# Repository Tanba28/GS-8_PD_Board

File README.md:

# GS-8_PD_Board
GS-8 Parachute Deployment Board

Master project -> [project-arrows/GS-8](https://github.com/project-arrows/GS-8)

## Overview
 * GS-8パラシュート開放基板

## Role
 * 気圧をロギングする。
 * 頂点検知を行う。
 * 開放用アクチュエータ(サーボモータ)を駆動する。

## Link
 * [Tanba28/GS-8_PM_Board](https://github.com/Tanba28/GS-8_PM_Board)
 * [Tanba28/GS-8_Motion_Logger](https://github.com/Tanba28/GS-8_Motion_Logger)
 * [Tanba28/GS-8_Barometer](https://github.com/Tanba28/GS-8_Barometer)
 * [Tanba28/GS-8_Relay_Board](https://github.com/Tanba28/GS-8_Relay_Board)
 * [ringo156/GS-8_ACCLRM_Board](https://github.com/ringo156/GS-8_ACCLRM_Board)
 * [takamasavvv/RCT-X_Logger](https://github.com/takamasavvv/RCT-X-Logger)
 * [takamasavvv/RCT-X-Telemetry](https://github.com/takamasavvv/RCT-X-Telemetry)
 
## LICENSE
MIT License

Copyright (c) 2019 Tanba28

Permission is hereby granted, free of charge, to any person obtaining a copy
of this software and associated documentation files (the "Software"), to deal
in the Software without restriction, including without limitation the rights
to use, copy, modify, merge, publish, distribute, sublicense, and/or sell
copies of the Software, and to permit persons to whom the Software is
furnished to do so, subject to the following conditions:

The above copyright notice and this permission notice shall be included in all
copies or substantial portions of the Software.

THE SOFTWARE IS PROVIDED "AS IS", WITHOUT WARRANTY OF ANY KIND, EXPRESS OR
IMPLIED, INCLUDING BUT NOT LIMITED TO THE WARRANTIES OF MERCHANTABILITY,
FITNESS FOR A PARTICULAR PURPOSE AND NONINFRINGEMENT. IN NO EVENT SHALL THE
AUTHORS OR COPYRIGHT HOLDERS BE LIABLE FOR ANY CLAIM, DAMAGES OR OTHER
LIABILITY, WHETHER IN AN ACTION OF CONTRACT, TORT OR OTHERWISE, ARISING FROM,
OUT OF OR IN CONNECTION WITH THE SOFTWARE OR THE USE OR OTHER DEALINGS IN THE
SOFTWARE.

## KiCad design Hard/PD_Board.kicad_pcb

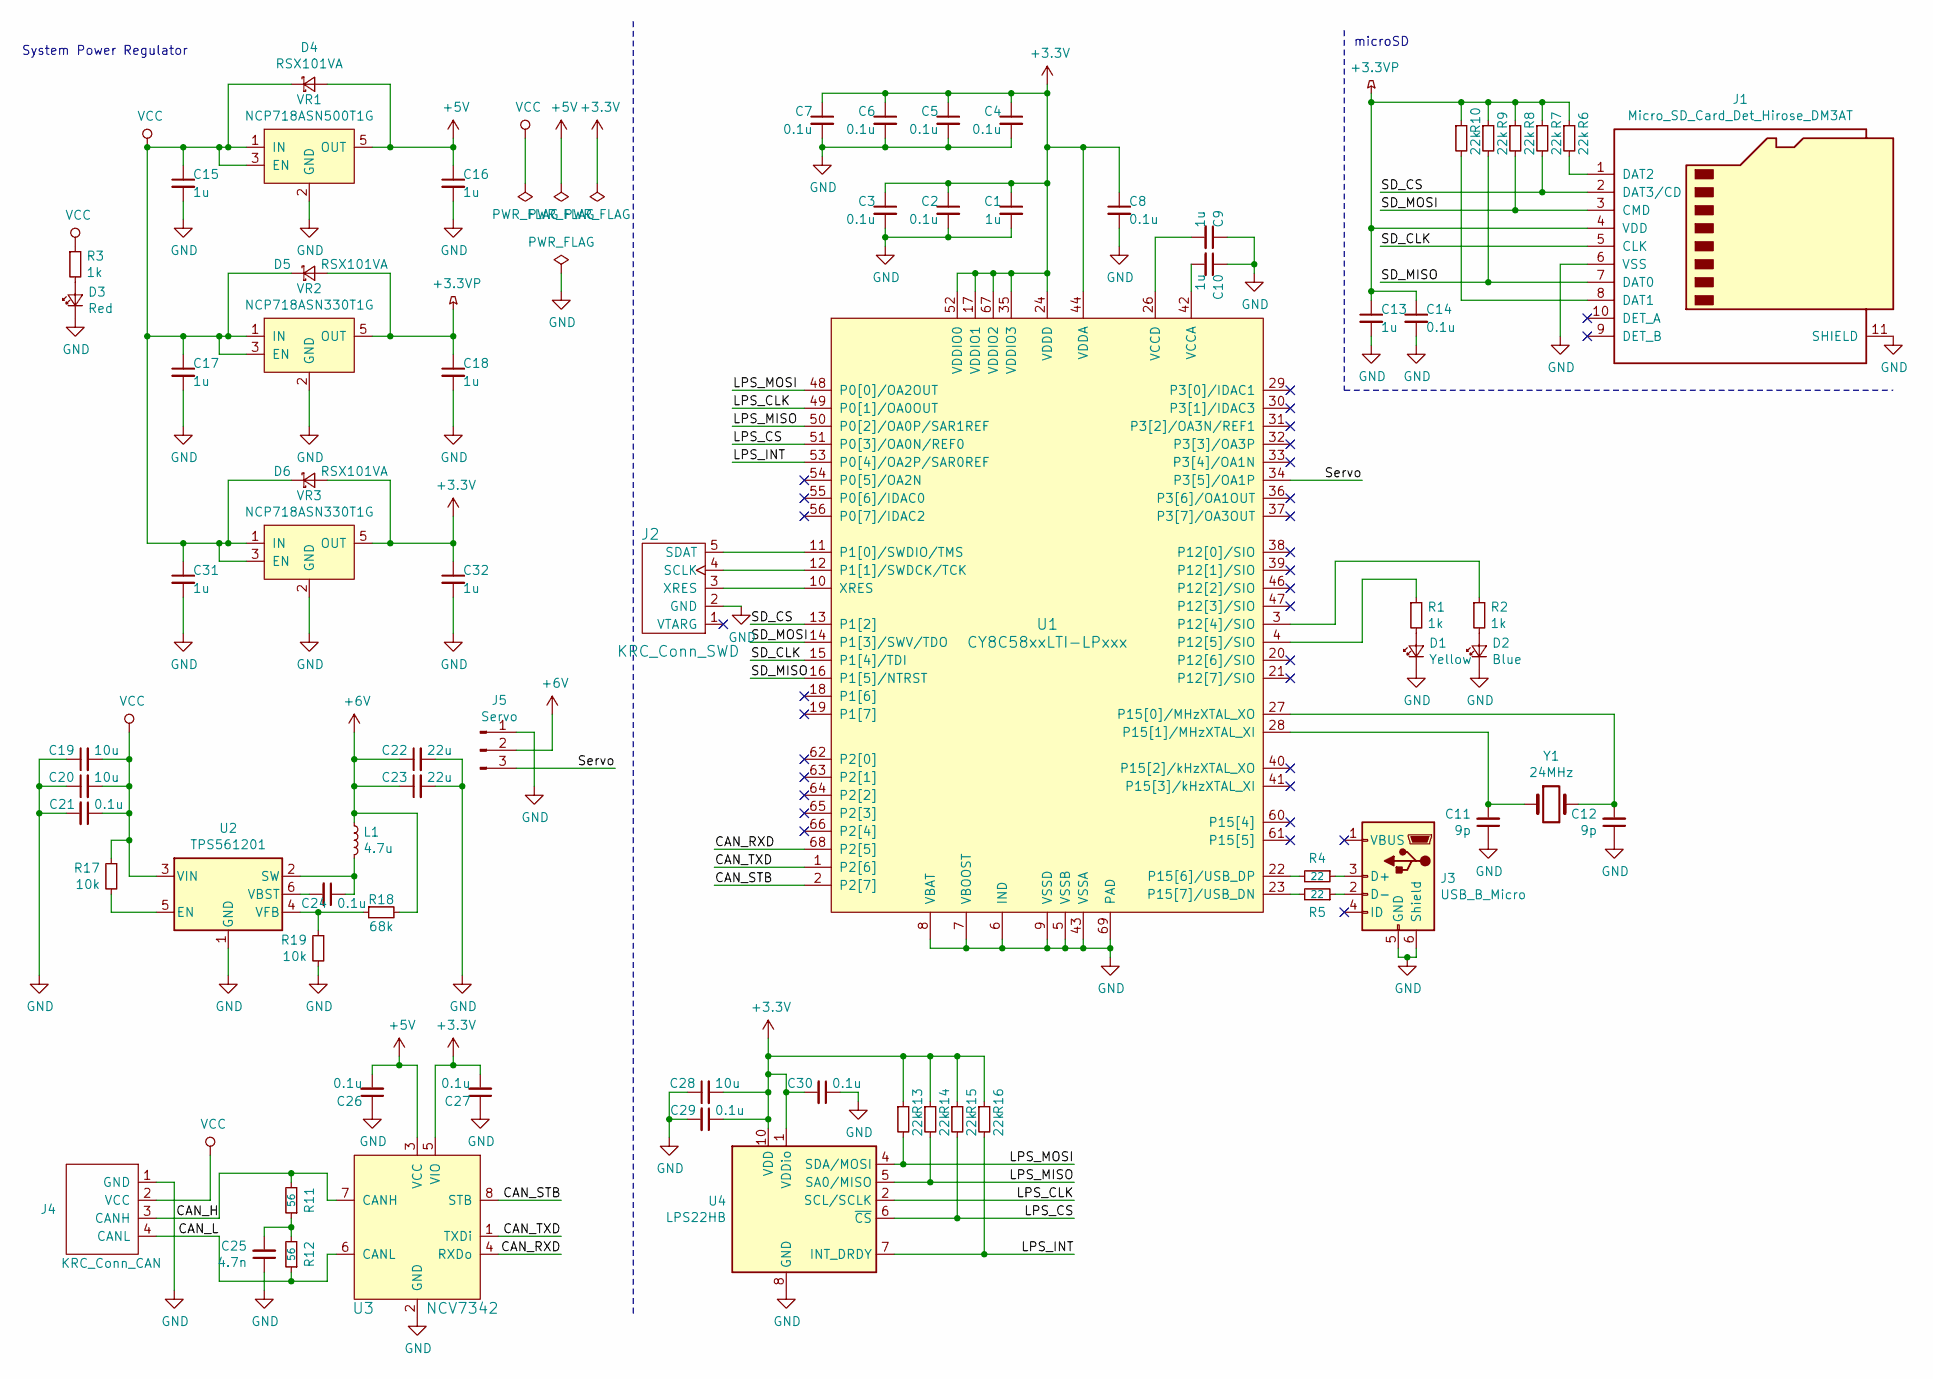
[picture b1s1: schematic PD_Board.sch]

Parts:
C1, C9, C10, C13, C15, C16, C17, C18, C31, C32: 1u; C_0402_1005Metric; MPN GRM155R61E105KA12D
C2, C3, C4, C5, C6, C7, C8, C14, C21, C24, C26, C27, C29, C30: 0.1u; C_0402_1005Metric; MPN GRM155R62A104KE14D
C11, C12: 9p; C_0402_1005Metric; MPN GRM1555C1H9R0DA01D
C19, C20, C28: 10u; C_0603_1608Metric; MPN GRM188R6YA106MA73D
C22, C23: 22u; C_0805_2012Metric; MPN GRM21BR61E226ME44K
C25: 4.7n; C_0402_1005Metric; MPN GRM155R71H472KA01D
D1: Yellow; LED_0603_1608Metric
D2: Blue; LED_0603_1608Metric
D3: Red; LED_0603_1608Metric
D4, D5, D6: RSX101VA; D_TUMD2; MPN RSX101VAM-30TR
J1: Micro_SD_Card_Det_Hirose_DM3AT; microSD_HC_Hirose_DM3AT-SF-PEJM5; MPN DM3AT-SF-PEJM5
J2: KRC_Conn_SWD; JST_JQ_05JQ-BT_1x05_P2.5mm_Vertical; MPN 05JQ-BT
J3: USB_B_Micro; Hirose_ZX_ZX62D-B-5P8; MPN ZX62D-B-5P8(30)
J4: KRC_Conn_CAN; JST_XH_S4B-XH-A_1x04_P2.50mm_Horizontal; MPN S4B-XH-A
J5: Servo; Hirose_DF1E_DF1E-3P-2.5DS_1x03_P2.5mm_Vertical; MPN DF1EC-3P-2.5DSA(35)
L1: 4.7u; L_Taiyo-Yuden_NR-50xx; MPN NRS5020T4R7MMGJ
R1, R2, R3: 1k; R_0402_1005Metric; MPN ERJ-2GEJ102X
R4, R5: 22; R_0402_1005Metric; MPN ERJ-2GEJ220X
R6, R7, R8, R9, R10, R13, R14, R15, R16: 22k; R_0402_1005Metric; MPN ERJ-2RKF2202X
R11, R12: 56; R_0402_1005Metric; MPN ERJ-2GEJ560X
R17, R19: 10k; R_0402_1005Metric; MPN ERJ-2GEJ103X
R18: 68k; R_0402_1005Metric; MPN ERJ-2GEJ103X
U1: CY8C58xxLTI-LPxxx; Cypress_QFN-68_EP_8x8_Pitch0.4mm; MPN CY8C5868LTI-LP039
U2: TPS561201; SOT-23-6; MPN TPS561201DDCT
U3: NCV7342; DFN-8-1EP_3x3mm_P0.65mm_EP1.55x2.4mm; MPN NCV7342MW3R2G
U4: LPS22HB; ST_HLGA-10_2.5x2.5mm_P0.6mm_LayoutBorder3x2y
VR1: NCP718ASN500T1G; TSOT-23-5; MPN NCP718ASN500T1G
VR2, VR3: NCP718ASN330T1G; TSOT-23-5; MPN NCP718ASN330T1G
Y1: 24MHz; Crystal_Murata_XRCHA; MPN XRCHA24M000F0A01R0

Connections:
+3.3VP: C13.1, C14.1, C18.1, D5.2 (A), J1.4 (VDD), R6.1, R7.1, R8.1, R9.1, R10.1, VR2.5 (OUT)
+3V3: C1.1, C2.1, C3.1, C4.1, C5.1, C6.1, C7.1, C8.1, C27.2, C28.2, C29.1, C30.2, C32.1, D6.2 (A), R13.1, R14.1, R15.1, R16.1, U1.17 (VDDIO1), U1.24 (VDDD), U1.35 (VDDIO3), U1.44 (VDDA), U1.52 (VDDIO0), U1.59 (VDDD), U1.67 (VDDIO2), U3.5 (VIO), U4.1 (VDDio), U4.10 (VDD), VR3.5 (OUT)
+5V: C16.1, C26.2, D4.2 (A), U3.3 (VCC), VR1.5 (OUT)
+6V: C22.1, C23.1, J5.2, L1.1, R18.2
/CAN_H: J4.3 (CANH), R11.2, U3.7 (CANH)
/CAN_L: J4.4 (CANL), R12.1, U3.6 (CANL)
/CAN_RXD: U1.68 (P2[5]), U3.4 (RXDo)
/CAN_STB: U1.2 (P2[7]), U3.8 (STB)
/CAN_TXD: U1.1 (P2[6]), U3.1 (TXDi)
/LPS_CLK: U1.49 (P0[1]/OA0OUT), U4.2 (SCL/SCLK)
/LPS_CS: R15.2, U1.51 (P0[3]/OA0N/REF0), U4.6 (~CS)
/LPS_INT: R16.2, U1.53 (P0[4]/OA2P/SAR0REF), U4.7 (INT_DRDY)
/LPS_MISO: R14.2, U1.50 (P0[2]/OA0P/SAR1REF), U4.5 (SA0/MISO)
/LPS_MOSI: R13.2, U1.48 (P0[0]/OA2OUT), U4.4 (SDA/MOSI)
/SD_CLK: J1.5 (CLK), U1.15 (P1[4]/TDI)
/SD_CS: J1.2 (DAT3/CD), R7.2, U1.13 (P1[2])
/SD_MISO: J1.7 (DAT0), R9.2, U1.16 (P1[5]/NTRST)
/SD_MOSI: J1.3 (CMD), R8.2, U1.14 (P1[3]/SWV/TDO)
/Servo: J5.3, U1.34 (P3[5]/OA1P)
GND: C1.2, C2.2, C3.2, C4.2, C5.2, C6.2, C7.2, C8.2, C9.1, C10.1, C11.1, C12.1, C13.2, C14.2, C15.2, C16.2, C17.2, C18.2, C19.1, C20.1, C21.2, C22.2, C23.2, C25.1, C26.1, C27.1, C28.1, C29.2, C30.1, C31.2, C32.2, D1.1 (K), D2.1 (K), D3.1 (K), J1.6 (VSS), J1.11 (SHIELD), J2.2 (GND), J3.5 (GND), J3.6 (Shield), J4.1 (GND), J5.1, R19.2, U1.5 (VSSB), U1.6 (IND), U1.7 (VBOOST), U1.8 (VBAT), U1.9 (VSSD), U1.25 (VSSD), U1.43 (VSSA), U1.45 (VSSD), U1.58 (VSSD), U1.69 (PAD), U2.1 (GND), U3.2 (GND), U3.9, U4.3 (GND), U4.8 (GND), U4.9 (GND), VR1.2 (GND), VR2.2 (GND), VR3.2 (GND)
unnamed: C9.2, U1.26 (VCCD), U1.57 (VCCD)
unnamed: C10.2, U1.42 (VCCA)
unnamed: C11.2, U1.28 (P15[1]/MHzXTAL_XI), Y1.1
unnamed: C12.2, U1.27 (P15[0]/MHzXTAL_XO), Y1.2
unnamed: C24.1, L1.2, U2.2 (SW)
unnamed: C24.2, U2.6 (VBST)
unnamed: C25.2, R11.1, R12.2
unnamed: D1.2 (A), R1.2
unnamed: D2.2 (A), R2.2
unnamed: D3.2 (A), R3.2
unnamed: J1.1 (DAT2), R6.2
unnamed: J1.8 (DAT1), R10.2
unnamed: J2.3 (XRES), U1.10 (XRES)
unnamed: J2.4 (SCLK), U1.12 (P1[1]/SWDCK/TCK)
unnamed: J2.5 (SDAT), U1.11 (P1[0]/SWDIO/TMS)
unnamed: J3.2 (D-), R5.1
unnamed: J3.3 (D+), R4.1
unnamed: R1.1, U1.4 (P12[5]/SIO)
unnamed: R2.1, U1.3 (P12[4]/SIO)
unnamed: R4.2, U1.22 (P15[6]/USB_DP)
unnamed: R5.2, U1.23 (P15[7]/USB_DN)
unnamed: R17.2, U2.5 (EN)
unnamed: R18.1, R19.1, U2.4 (VFB)
VCC: C15.1, C17.1, C19.2, C20.2, C21.1, C31.1, D4.1 (K), D5.1 (K), D6.1 (K), J4.2 (VCC), R3.1, R17.1, U2.3 (VIN), VR1.1 (IN), VR1.3 (EN), VR2.1 (IN), VR2.3 (EN), VR3.1 (IN), VR3.3 (EN)

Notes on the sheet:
System Power Regulator
microSD

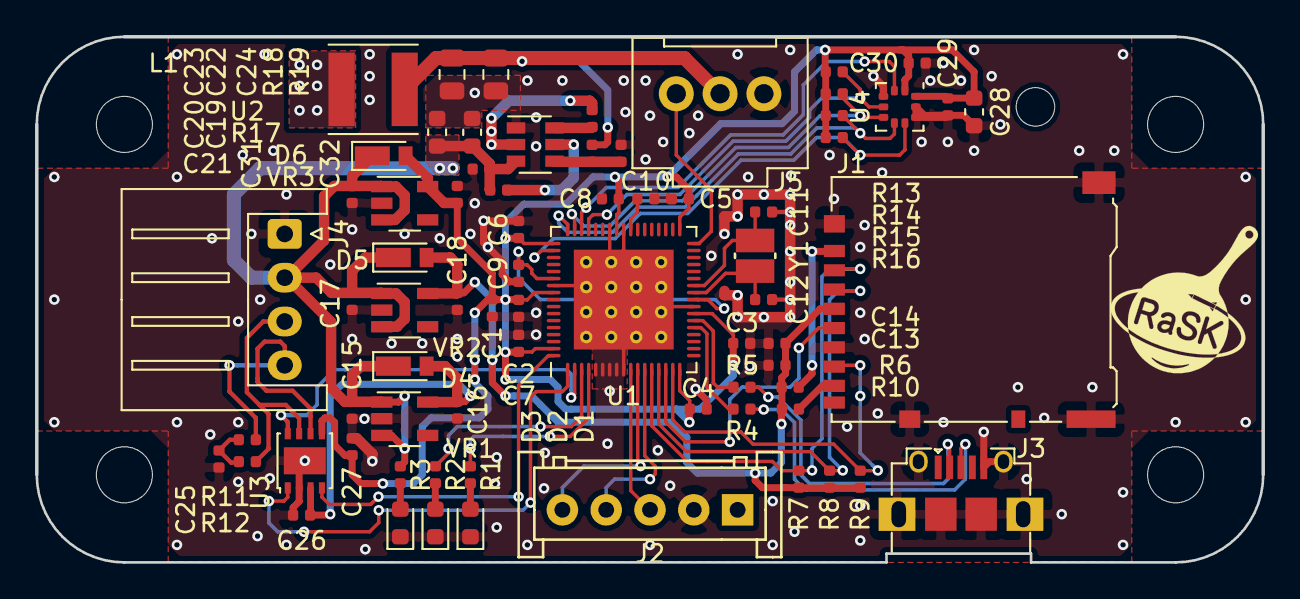
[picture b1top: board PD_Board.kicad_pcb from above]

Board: 2 copper layers, 70.0 x 30.0 mm, 71 parts (0 on the bottom side), 44 nets.

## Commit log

2019-09-25 [update] gitignoreからライブラリキャッシュを削除
2019-09-25 回路を設計中
2019-09-29 [add] 逆流防止用ダイオード追加。回路図仮完成
2019-10-03 [add] 配線完了
2019-10-04 [update] プルアップ抵抗ちゃんとしました
2019-10-04 [update] PDF出力
2019-10-12 [add] ガーバー出力
2019-10-12 [add] USBに切り欠きを追加.ガーバー出力
2019-10-12 [update] READMEを整備
2020-06-04 submoduleを追加
2020-06-04 プロジェクトを作成
2020-06-05 ピンアサイン、FreeRTOSを導入
2020-06-05 LPS22HB submoduleを追加
2020-06-05 LPS22HB動かした
2020-06-05 submoduleの変更を反映
2020-06-07 LPS22HBのFIFOを動かした
2020-06-14 SDカード書き込みのプロジェクト追加。動作確認
